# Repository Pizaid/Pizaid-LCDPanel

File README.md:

Pizaid LCD Controller
=====================

LCD Controller on Raspberry Pi with Pizaid Controller

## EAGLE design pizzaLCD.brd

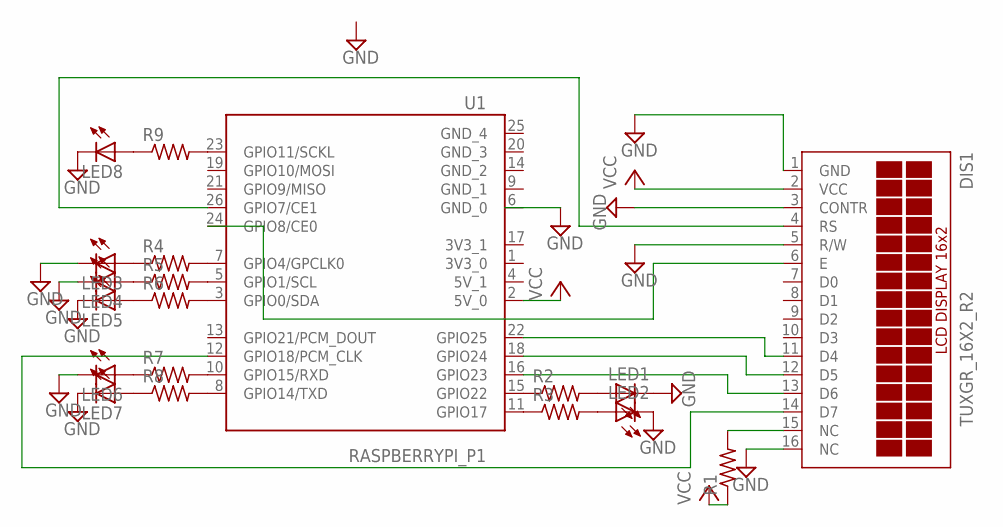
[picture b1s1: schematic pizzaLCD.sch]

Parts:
DIS1: TUXGR_16X2_R2
LED1, LED2, LED3, LED4, LED5, LED6, LED7, LED8: LED3MM
R1: R; 250-80
R2, R3, R4, R5, R6, R7, R8, R9: R/5; 0204/5
U1: RASPBERRYPI_P1; 2X13

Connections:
GND: DIS1.1 (GND), DIS1.3 (CONTR), DIS1.5 (R/W), DIS1.16 (NC), LED1.K (C), LED2.K (C), LED3.K (C), LED4.K (C), LED5.K (C), LED6.K (C), LED7.K (C), LED8.K (C)
unnamed: DIS1.4 (RS), U1.26 (GPIO7/CE1)
unnamed: DIS1.6 (E), U1.24 (GPIO8/CE0)
unnamed: R2.1, U1.15 (GPIO22)
unnamed: DIS1.12 (D5), U1.18 (GPIO24)
unnamed: DIS1.13 (D6), U1.16 (GPIO23)
unnamed: DIS1.11 (D4), U1.22 (GPIO25)
unnamed: LED1.A, R2.2
unnamed: DIS1.15 (NC), R1.P$2 (2)
unnamed: R3.1, U1.11 (GPIO17)
unnamed: LED2.A, R3.2
unnamed: R4.2, U1.7 (GPIO4/GPCLK0)
unnamed: R5.2, U1.5 (GPIO1/SCL)
unnamed: R6.2, U1.3 (GPIO0/SDA)
unnamed: R7.2, U1.10 (GPIO15/RXD)
unnamed: R8.2, U1.8 (GPIO14/TXD)
unnamed: R9.2, U1.23 (GPIO11/SCKL)
unnamed: LED4.A, R5.1
unnamed: LED3.A, R4.1
unnamed: LED5.A, R6.1
unnamed: LED6.A, R7.1
unnamed: LED7.A, R8.1
unnamed: LED8.A, R9.1
unnamed: DIS1.14 (D7), U1.12 (GPIO18/PCM_CLK)
VCC: DIS1.2 (VCC), R1.P$1 (1), U1.2 (5V_0)

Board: 2 copper layers, 19 parts (0 on the bottom side), 25 nets, no tracks yet.

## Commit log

2014-03-13 added program about LCD panel
2014-03-14 added kairozu, not completed yet
2014-07-07 Add .gitignore
2014-07-07 Add README
2014-07-12 Add pizaid python library
2014-07-12 Move main program to program
2014-07-12 Add setup.py and some test code
2014-07-18 Add dbus library
2014-07-18 Add classes
2014-08-02 add io and dbus server
2014-08-02 added state_multihandler.py
2014-08-02 test commit
2014-08-08 Change the communication library from dbus to thrift
2014-08-08 update ioserver and prototyped
2014-08-09 Add updating lcd panel
2014-08-09 GPIO works well
